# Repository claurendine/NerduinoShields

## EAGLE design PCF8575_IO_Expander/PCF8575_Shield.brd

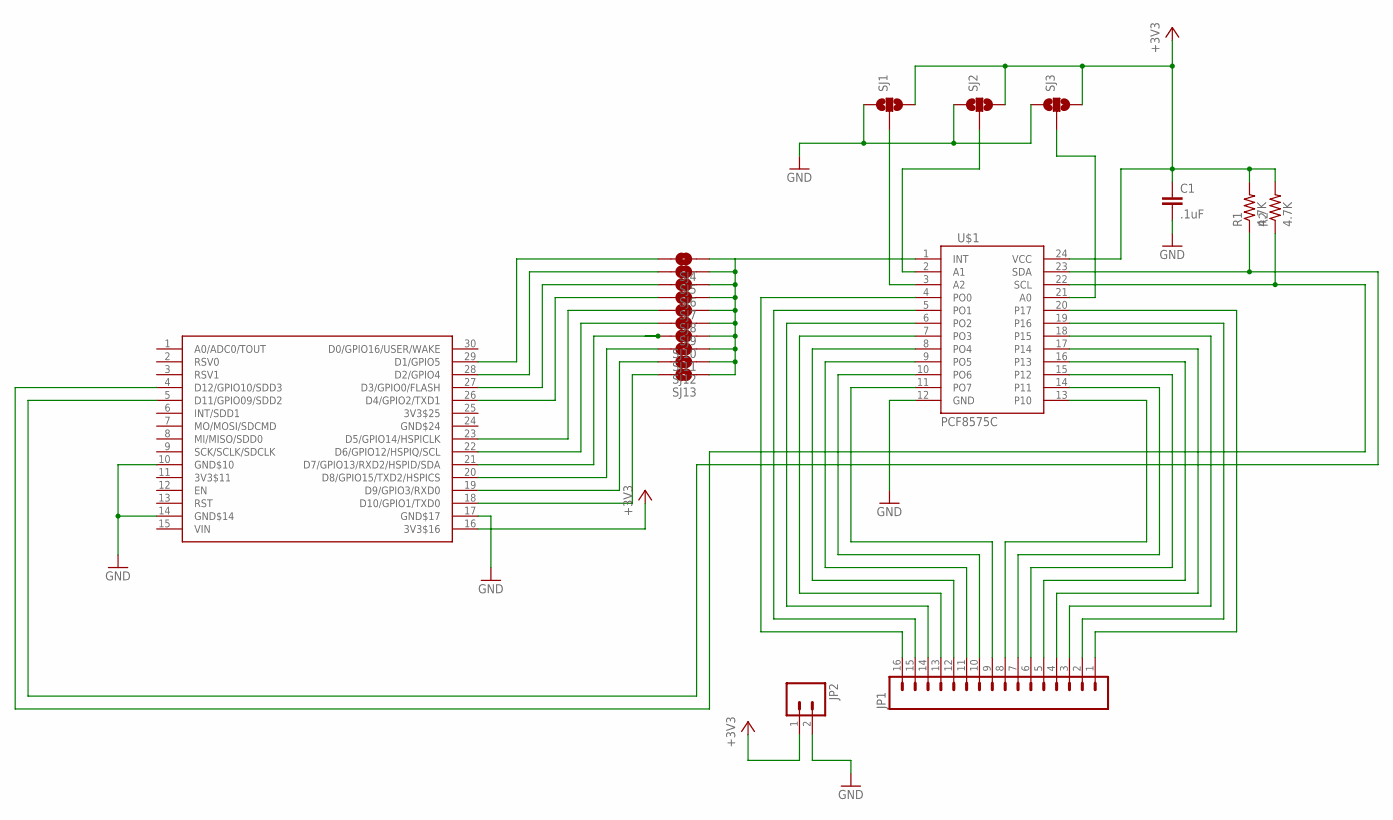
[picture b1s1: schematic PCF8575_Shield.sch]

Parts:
C1: .1uF; 0603-CAP
JP1: M161X16_NO_SILK; 1X16_NO_SILK
JP2: M02PTH; 1X02
R1, R2: 4.7K; 0603-RES
SJ1, SJ2, SJ3: SOLDERJUMPER_2WAYPASTE1&2; SJ_3_PASTE1&2
SJ4, SJ5, SJ6, SJ7, SJ8, SJ9, SJ10, SJ11, SJ12, SJ13: SOLDERJUMPERNO; SJ_2S-NO
U$1: PCF8575C; SO-24DW
U$2: NERDSHIELD; NERDUINO_STACK

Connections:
+3V3: C1.1, JP2.1, R1.2, R2.2, SJ1.3, SJ2.3, SJ3.3, U$1.24 (VCC), U$2.16 (3V3$16)
GND: C1.2, JP2.2, SJ1.1, SJ2.1, SJ3.1, U$1.12 (GND), U$2.10 (GND$10), U$2.14 (GND$14), U$2.17 (GND$17)
unnamed: JP1.1, U$1.20 (P17)
unnamed: R1.1, U$1.23 (SDA), U$2.5 (D11/GPIO09/SDD2)
unnamed: SJ4.1, SJ5.1, SJ6.1, SJ7.1, SJ8.1, SJ9.1, SJ10.1, SJ11.1, SJ12.1, SJ13.1, U$1.1 (INT)
unnamed: SJ3.2, U$1.21 (A0)
unnamed: R2.1, U$1.22 (SCL), U$2.4 (D12/GPIO10/SDD3)
unnamed: SJ2.2, U$1.2 (A1)
unnamed: JP1.2, U$1.19 (P16)
unnamed: SJ1.2, U$1.3 (A2)
unnamed: JP1.3, U$1.18 (P15)
unnamed: JP1.4, U$1.17 (P14)
unnamed: JP1.5, U$1.16 (P13)
unnamed: JP1.6, U$1.15 (P12)
unnamed: JP1.7, U$1.14 (P11)
unnamed: JP1.8, U$1.13 (P10)
unnamed: JP1.9, U$1.11 (PO7)
unnamed: JP1.10, U$1.10 (PO6)
unnamed: JP1.11, U$1.9 (PO5)
unnamed: JP1.12, U$1.8 (PO4)
unnamed: JP1.13, U$1.7 (PO3)
unnamed: JP1.14, U$1.6 (PO2)
unnamed: JP1.15, U$1.5 (PO1)
unnamed: JP1.16, U$1.4 (PO0)
unnamed: SJ4.2, U$2.29 (D1/GPIO5)
unnamed: SJ5.2, U$2.28 (D2/GPIO4)
unnamed: SJ6.2, U$2.27 (D3/GPIO0/FLASH)
unnamed: SJ7.2, U$2.26 (D4/GPIO2/TXD1)
unnamed: SJ8.2, U$2.23 (D5/GPIO14/HSPICLK)
unnamed: SJ9.2, U$2.22 (D6/GPIO12/HSPIQ/SCL)
unnamed: SJ10.2, U$2.21 (D7/GPIO13/RXD2/HSPID/SDA)
unnamed: SJ11.2, U$2.20 (D8/GPIO15/TXD2/HSPICS)
unnamed: SJ12.2, U$2.19 (D9/GPIO3/RXD0)
unnamed: SJ13.2, U$2.18 (D10/GPIO1/TXD0)

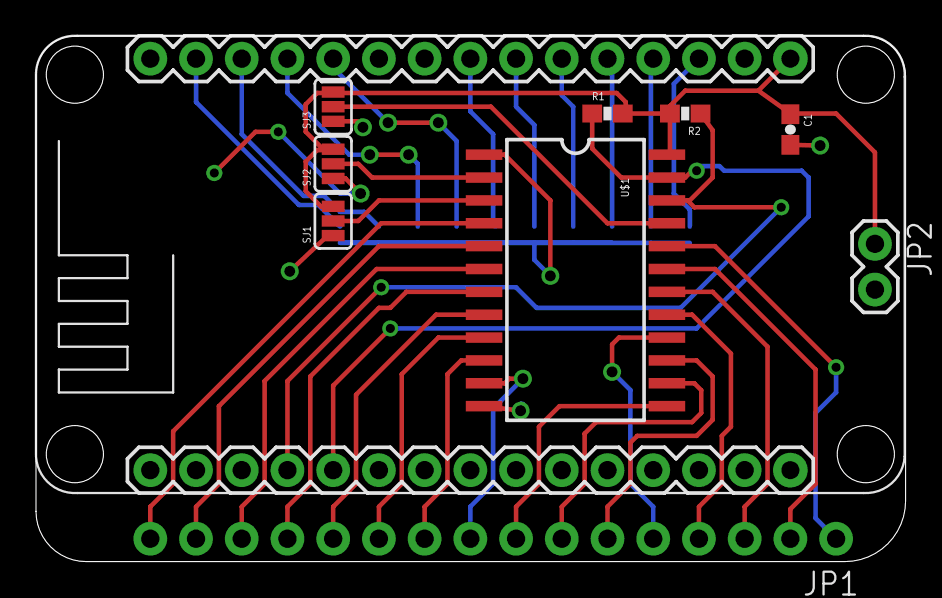
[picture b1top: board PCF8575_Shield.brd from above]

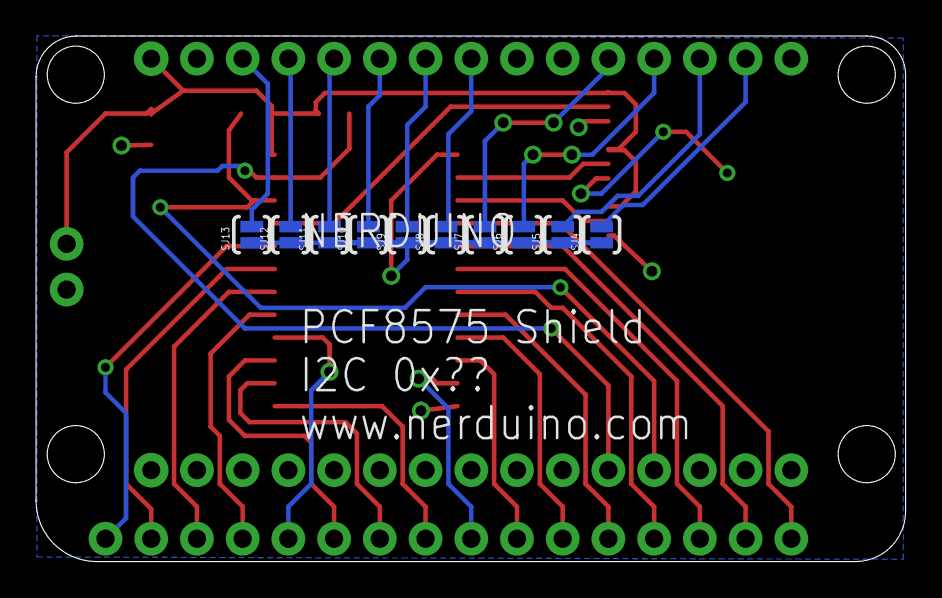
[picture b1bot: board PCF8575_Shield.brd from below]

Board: 2 copper layers, 48.3 x 29.2 mm, 20 parts (10 on the bottom side), 34 nets.

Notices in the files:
parts and their libraries:
SparkFun-Connectors: Licensing: Creative Commons ShareAlike 4.0 International - https://creativecommons.org/licenses/by-sa/4.0
